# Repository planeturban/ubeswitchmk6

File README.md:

# Main functions
* Atari DIN13 to VGA
* 3.5mm A/V connector with volume control.
* Automatic detection of resolution.

# v1.4 update
Added a AG-pad (AG after the guy who requested it) cut trace and connect the other pad to feed h-sync to PB2 instead of v-sync. Updates to firmware is needed.

Please be aware that the PCB is **unrouted** since different PCB houses has different tolerances and it **might** mess up the end product. 

# Manual
Plug device into your Atari.

Turn your Atari on.

Press .25-1.999[...] seconds: Switch mode.

Press +2 seconds: store current mode as default at cold boot.

# Assembly tips
For least amount of wobbliness:
1. Backside SMD stuff (TS5V330, ATtiny85 and 78l05). 
2. Flip board over, solder all SMD.
3. DIN13
4. Lastly solder volume pot and VGA. Flipping of board is optional if you're a good at soldering.

# BOM
Part|Value|Device|Package|Description|MF|MPN|OC_FARNELL|OC_NEWARK|PACKAGE|PROD_ID|SUPPLIER|
--|--|----|----|---|--|---|-|-|-|-|-|
ATARIOUT|DIN13T|DIN13T|DIN13|||||||||
IC2|78L05F|78L05F|SOT89|POSITOIV-VOLTAGE REGULATORS||||||||
JP1||PINHD-1X2|1X02|PIN HEADER||||||||
S2||K2-1823SA||||||||||
TM1-3|100R|TRIMPOTTC33X|TC33X|SMT trimmer potentiometer part number TC33X||||||||
TS5V330||V330|SOIC16N|||||||||
U$1||PJ-320D||Audio jack - 3.5mm TRRS variety - two rings.||||||CONN-10676||
U$2|DB-1001N|DB-1001N|THUMB_POT|Multicomp||||||||
U1|ATTINY85-20SU|ATTINY85-20SU|SOIC127P798X216-8N|8-bit Microcontroller with In-System Programmable Flash||ATTINY85-20SU|1455164|58M3797|SOIC-8||Atmel|
X1||F15HDVS|HDF15V|SUB-D|||unknown|unknown||||

# Troubleshooting
 Symptom        | Solution|
| ------------- |:------|
|Constant switching|Check ATtiny soldering, probably rebooting. +5V and GND are possible offenders.|
|Dark picture.|Check soldering on multiplexer, pin 8 and 16 (GND and VCC).|
|Physical switch not working, software switching works.| Check soldering at ATtiny PB4 and soldering at the tactile switch itself.|
|Niether software or hardware switching works.| Check soldering ATtiny PB3 and multiplexer pin 1.|
|Niether software or hardware switching works, boots in low res.| Did you remember to program your ATtiny?|
|Software switch not working|Check soldering on ATtiny PB2 and V-sync on DIN|
|Hardware switch slow.|Did you set fuses ("Burn bootloader" in Arduino IDE) before programming ATtiny? Processor is probably running in 1MHz.|
|Won't hold saved state, switches to hires after cold boot.|Try upping bootWait, probably some timing issues at boot. A recap of PSU might be in place as well.|

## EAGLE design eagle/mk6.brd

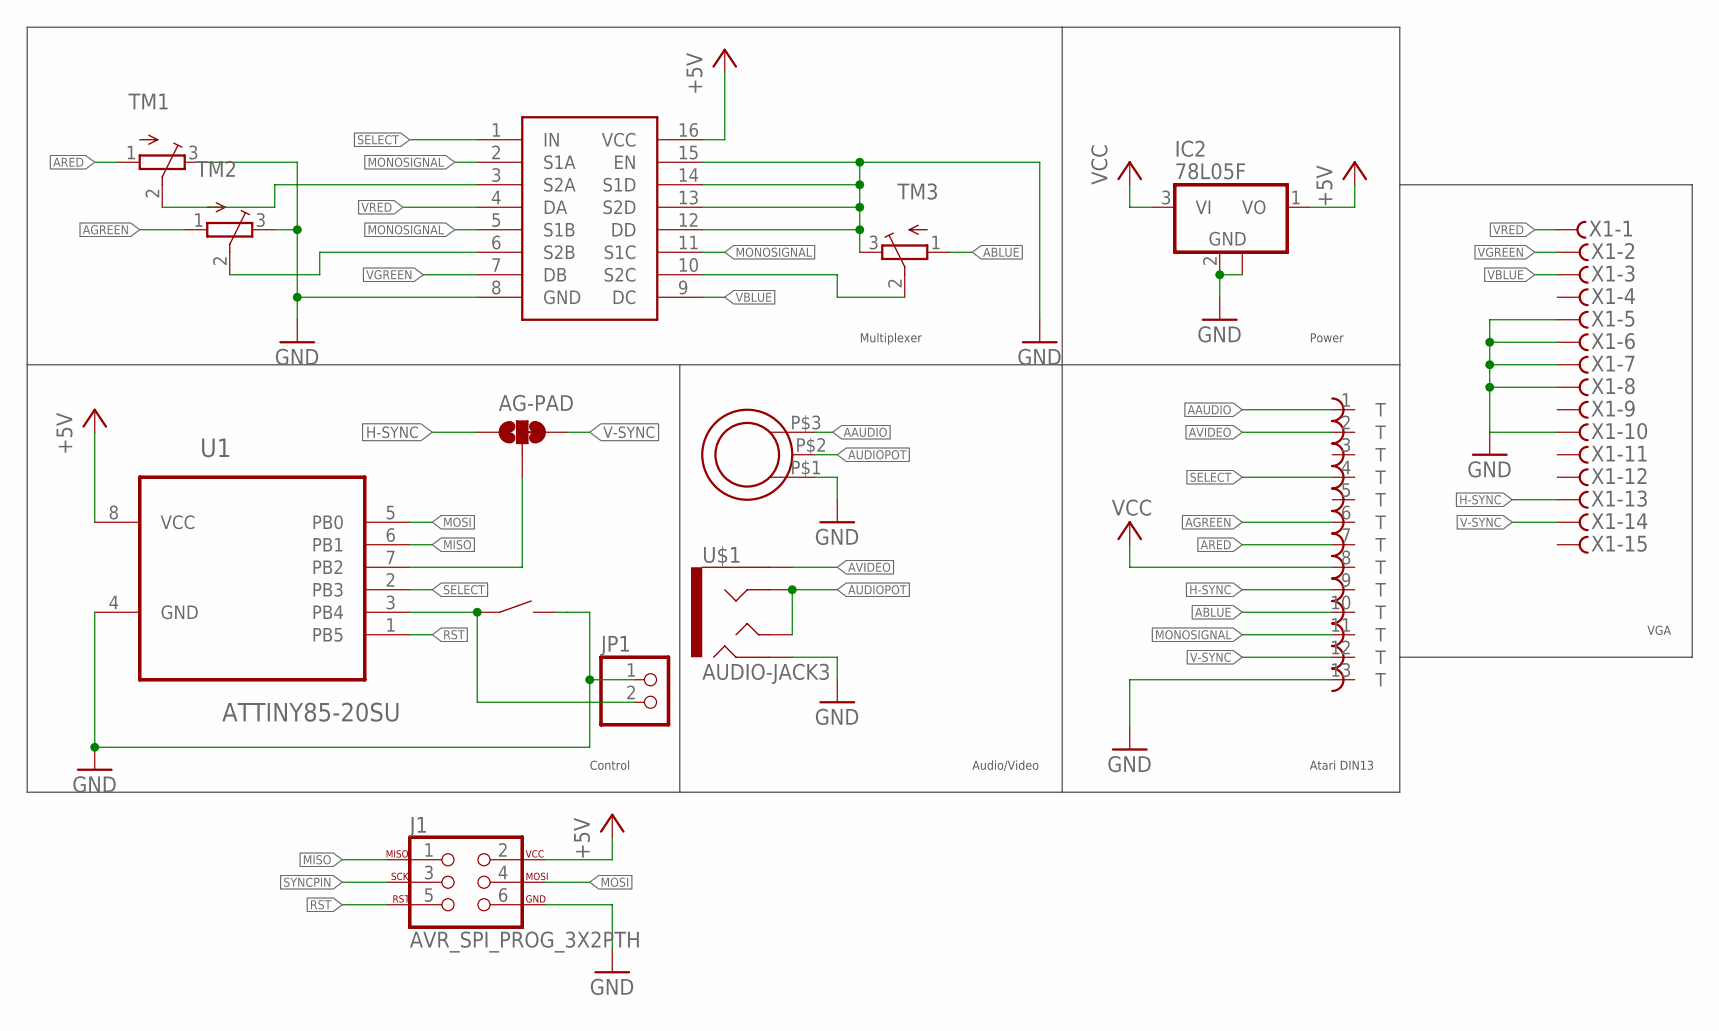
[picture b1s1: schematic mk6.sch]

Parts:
AG-PAD: JUMPER-SMT_3_1-NC_TRACE_SILK; SMT-JUMPER_3_1-NC_TRACE_SILK
ATARIOUT: DIN13T; ADADS
IC2: 78L05F; SOT89
J1: AVR_SPI_PROG_3X2PTH; 2X3
JP1: PINHD-1X2; 1X02
S2: K2-1823SA
TM1, TM2, TM3: TRIMPOTTC33X; TC33X
TS5V330: V330; SOIC16N
U1: ATTINY85-20SU; SOIC127P798X216-8N
U$1: AUDIO-JACK3; AUDIO-JACK-TRRS-SMD
U$2: DB-1001N; THUMB_POT
X1: F15HDVS; HDF15V

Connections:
+5V: IC2.1 (VO), J1.2, TS5V330.16 (VCC), U1.8 (VCC)
AAUDIO: ATARIOUT.1, U$2.P$3 (3)
ABLUE: ATARIOUT.10, TM3.1 (A)
AGREEN: ATARIOUT.6, TM2.1 (A)
ARED: ATARIOUT.7, TM1.1 (A)
AUDIOPOT: U$1.RING1, U$1.TIP, U$2.P$2 (2)
AVIDEO: ATARIOUT.2, U$1.EARTH
GND: ATARIOUT.13, IC2.2 (GND), IC2.2@1 (GND), J1.6, JP1.1, S2.P$2 (2), TM1.3 (E), TM2.3 (E), TM3.3 (E), TS5V330.8 (GND), TS5V330.12 (DD), TS5V330.13 (S2D), TS5V330.14 (S1D), TS5V330.15 (EN), U1.4 (GND), U$1.RING2, U$2.P$1 (1), X1.5, X1.6, X1.7, X1.8, X1.10
H-SYNC: AG-PAD.1, ATARIOUT.9, X1.13
MISO: J1.1, U1.6 (PB1)
MONOSIGNAL: ATARIOUT.11, TS5V330.2 (S1A), TS5V330.5 (S1B), TS5V330.11 (S1C)
MOSI: J1.4, U1.5 (PB0)
unnamed: JP1.2, S2.P$1 (1), U1.3 (PB4)
PBLUE: TM3.2 (S), TS5V330.10 (S2C)
PGREEN: TM2.2 (S), TS5V330.6 (S2B)
PRED: TM1.2 (S), TS5V330.3 (S2A)
RST: J1.5, U1.1 (PB5)
SELECT: ATARIOUT.4, TS5V330.1 (IN), U1.2 (PB3)
SYNCPIN: AG-PAD.2, J1.3, U1.7 (PB2)
V-SYNC: AG-PAD.3, ATARIOUT.12, X1.14
VBLUE: TS5V330.9 (DC), X1.3
VCC: ATARIOUT.8, IC2.3 (VI)
VGREEN: TS5V330.7 (DB), X1.2
VRED: TS5V330.4 (DA), X1.1

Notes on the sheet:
Audio/Video
Atari DIN13
Power
VGA
Multiplexer
Control

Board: 2 copper layers, 14 parts (6 on the bottom side), 24 nets, no tracks yet.

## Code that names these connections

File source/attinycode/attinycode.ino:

/*
   Compiled with MicroCore: 980 bytes. (Not working..)
   Compiled for Attiny85: 956 bytes.
                          5244 bytes with debug.
How to read this code:
1. Don't. It's ugly.
2. When "pin" is referred in code (or text) it's the Atari side of things. The ATtiny's pins are always referred to as PBX. 

*/


//#define LEGACY // Uncomment this if your device does not have a ISP header.
//#define ALT_DETECT





//#define DEBUG


// Timings.
#define switchTime 250000
#define saveTime 2000000
#define bootWait 4000 // Wait for computer to stabilize, 3-4s seems ok.





#include <EEPROM.h>




#if defined(DEBUG) && !defined(LEGACY)
#include <SoftwareSerial.h>
SoftwareSerial mySerial(PB0, PB1); // RX, TX
#endif



#ifdef LEGACY
#define buttonPin PB0       // Connected to switch
#define selectPin PB1     // TS5V330 pin 1
#define pulsePin PB2       // VSync
#else
#define pulsePin PB2       // VSync
#define selectPin PB3     // TS5V330 pin 1
#define buttonPin PB4       // Connected to switch
#endif



unsigned long buttonPressedTime;
int pulseThreshold = 15000;

byte state;
byte lastState;
byte tosState;

#ifdef DEBUG
bool done = false;
String buff;
char data;
int i = 0;
#endif

unsigned long pulse = 0;


void setup() {
// IDEA: check if a jumper is placed on the ISP header to enter some kind of other operations mode. 


#if defined (DEBUG) && !defined(LEGACY)
  mySerial.begin(9600);
  mySerial.println("Boot");
#endif

  PORTB |= bit(buttonPin); // Input pullup.

  state = EEPROM.read(0);
// Instead of sending +5V to the Atari, let the pullup on pin4 handle the high part.
  bitWrite(DDRB, selectPin, state); 


#if defined (DEBUG) && !defined(LEGACY)
  mySerial.print("Waiting for ");
  mySerial.print(bootWait);
  mySerial.println(" milliseconds.");
#endif
  _delay_ms(bootWait);
  lastState = state;
#if defined (DEBUG) && !defined(LEGACY)
  if ( ! bitRead(PINB, buttonPin) )
    mySerial.println("Button held, prompt...");

  mySerial.print("> ");

/*
// Really need to fix this part.
  while ( ! done ) {
    if ( mySerial.available() > 0 ) {
      data = mySerial.read();
      mySerial.print(data);
      if ( int(data) != 10 ) {
        buff[i] = data;
        i++;
      } else {
        if ( buff[0] == "q" ) {
          done = true;
        } else if ( buff[0] == "h" ) {
          printHelp();
          clearBuff();
        } else if ( buff[0] == "b" ) {
          PORTB ^= bit(selectPin);
          clearBuff();
        } else if ( buff[0] == "s" ) {
          if ( buff[2] == " " )
            buff = buff.substring(2);
          else
            buff = buff.substring(1);
          int v = buff.toInt();
          clearBuff();
        } else {

          mySerial.println("Error in command.");
        }
      }
    }

  }
*/

    while ( ! bitRead(PINB, buttonPin) ); // Wait for button to be released.


  mySerial.println("Loop.");
#endif



}




#ifdef DEBUG
void clearBuff() {
  buff = "";
  i = 0;
  mySerial.print("> ");
}



void printHelp() {
  mySerial.println("Help");
  mySerial.println("-----------");
  mySerial.println("b       - Simulate button press.");
  mySerial.println("p       - Print information.");
  mySerial.println("q       - Quit prompt.");
  mySerial.println("s <num> - Set pulse threashold.");

}
#endif

void loop() {

  /*
     Detection..
  */
  pulse = 0;
#ifdef ALT_DETECT
  while ( pulse < 10000 ) // 10000 since sometimes you'd get 14 from getPulse();
    pulse = getPulse();
#else

  while ( ! pulse )
    pulse = pulseIn(pulsePin, HIGH, 1000000L);
#endif


  state = pulse < pulseThreshold;



  if ( state != lastState ) {
#if defined (DEBUG) && !defined(LEGACY)
    mySerial.println("State change");
    mySerial.print("New state: ");
    mySerial.println(state);
    mySerial.print("Pulse: ");
    mySerial.println(pulse);
#endif
    bitWrite(DDRB, selectPin, state);

  }
  lastState = state;

  /*
       Button, save and switch.
  */

  if ( !bitRead(PINB, buttonPin) ) {
    buttonPressedTime = micros();
    while ( ! bitRead(PINB, buttonPin)); // Ugly debounce
    if ( micros() > saveTime  + buttonPressedTime ) {
#if defined (DEBUG) && !defined(LEGACY)
      mySerial.println("Save");
      mySerial.print("Value: ");
      mySerial.println(state);
#endif
      EEPROM.write(0, state);
    } else if ( micros() > buttonPressedTime + switchTime ) {
#if defined (DEBUG) && !defined(LEGACY)
      mySerial.println("Switch");
#endif
      DDRB ^= bit(selectPin);

      _delay_ms(1000); // Wait for computer to reboot and get its shit togheter.
    }
  }
}

unsigned long getPulse() {
  pulse = bitRead(PINB, pulsePin);
  while ( bitRead(PINB, pulsePin) == pulse);
  unsigned long pstart = micros();
  while ( bitRead(PINB, pulsePin) != pulse);
  return ( micros() - pstart);
}

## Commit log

2018-03-25 I cna't spel
2018-03-25 Added .gitignore
2018-03-27 Spring cleaning of code.
2018-04-20 More troubleshooting.
2020-01-03 v1.4. Added AG-pad, different button than 1.3b
2020-01-03 Update BOM
2020-01-03 v1.4 updates in README
2020-12-02 Removed routing since PCB houses differ..
2021-01-05 Create LICENSE
2021-03-18 Create LICENSE_Compliance.txt
    Update to the license compliance information

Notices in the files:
parts and their libraries:
SparkFun-Connectors: Licensing: Creative Commons ShareAlike 4.0 International - https://creativecommons.org/licenses/by-sa/4.0
